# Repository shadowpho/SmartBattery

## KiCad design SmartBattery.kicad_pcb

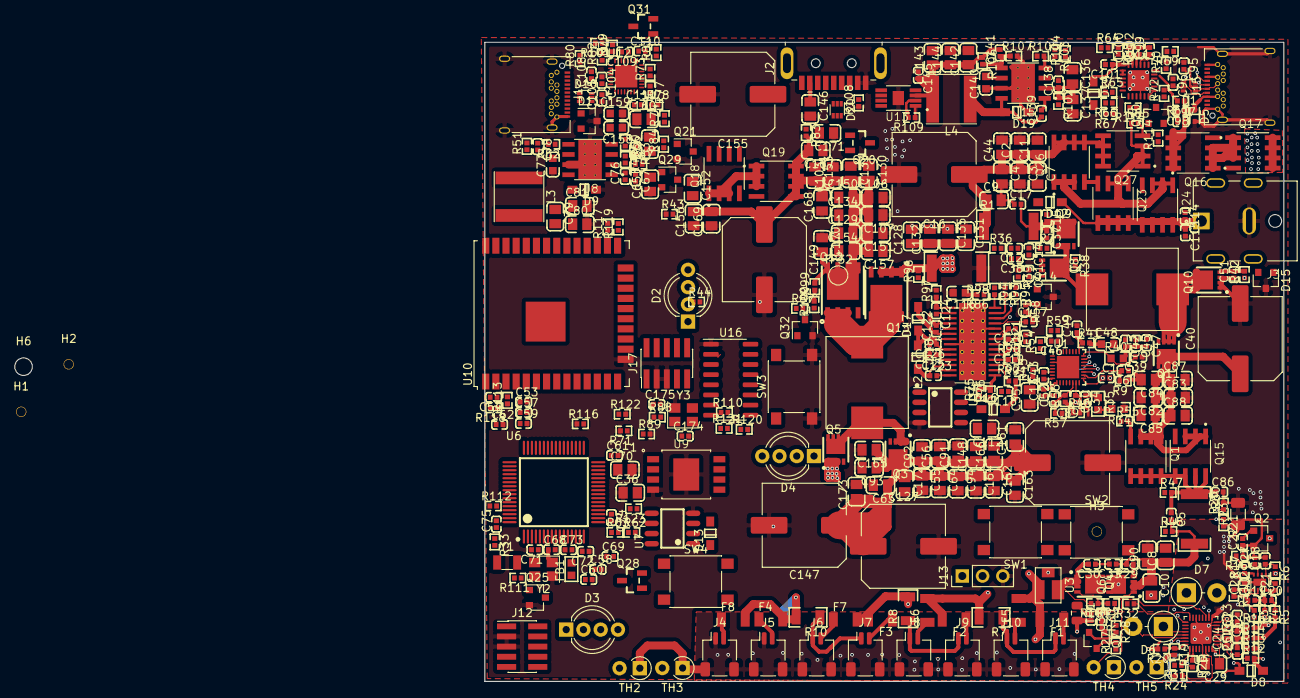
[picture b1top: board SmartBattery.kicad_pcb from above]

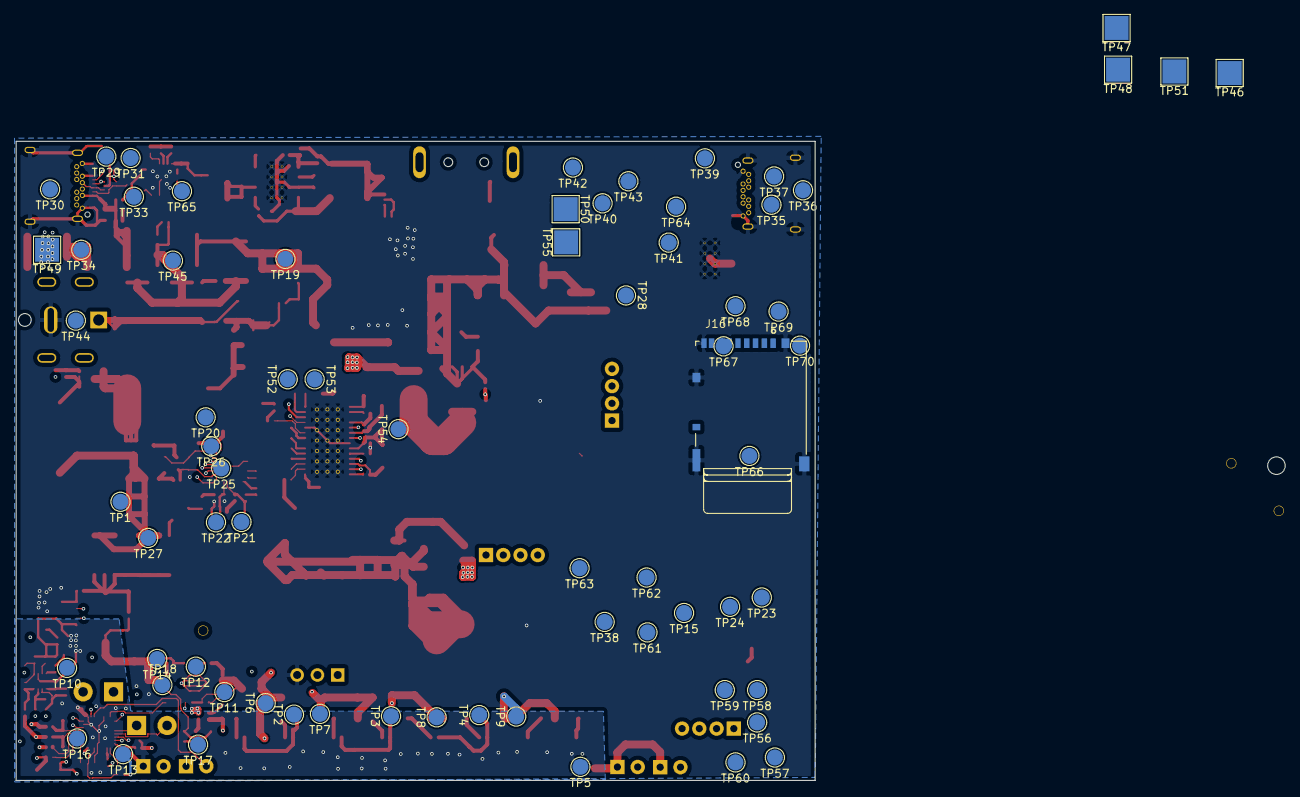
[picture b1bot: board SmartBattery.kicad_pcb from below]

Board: 4 copper layers, 100.0 x 80.0 mm, 481 parts (70 on the bottom side), 267 nets.

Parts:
C1, C6, C34: 0.1uF 6.3v; 0402_C
C2, C3, C4, C7, C8, C9, C10, C11, C65, C66, C82, C83, C84, C85, C136, C137: 10u; 0805_C
C5: 0.1u; 0402_C
C12: DNP; 0402_C
C13, C86, C97, C98, C99, C100, C101, C102, C108, C109, C110, C111: 1uF 25v; 0402_C
C14, C15, C17, C38, C124: 33nF; 0402_C
C16, C40, C89, C127, C147, C149, C155: 470u; C_Elec_10x10.2
C18, C19, C20, C21, C23, C24, C25, C26, C32, C53, C54, C57, C59, C61, C62, C69, C72, C73, C74, C75: 0.1u 6.3v; 0402_C
C22, C43, C46, C145: 0.1uF 25v; 0402_C
C27, C28: 0.1u 20v; 0402_C
C29, C35: 2.2u 50v; 0805_C
C30, C33: 0.1u 50v; 0402_C
C31, C122, C123: 0.1uF; 0402_C
C36, C70, C112: 2.2u 6.3v; 0805_C
C37, C41, C42, C45, C51, C95, C96, C104, C105, C117: 150pF; 0402_C
C39: 33pF; 0402_C
C44, C55, C56, C63, C64, C79, C80, C81, C87, C88, C90, C91, C92, C93, C94, C142, C143, C144, C146, C148, C161, C162, C163, C164, C165, C166, C172, C173: 22u; 0805_C
C47: 1.5nF; 0402_C
C48: 680pF; 0603_C
C49: 15pF; 0402_C
C50, C52: 1uF 16v; 0402_C
C58, C60: 15 pF 0402; 0402_C
C67, C76, C138, C139: 0.1u 25v; 0402_C
C68, C71, C174, C175: 12pF 0402; 0402_C
C77, C140: 8.2nF; 0603_C
C78, C141: 220pF; 0402_C
C103, C106, C107, C128, C129, C130, C131, C132, C133, C134, C135, C150, C151, C152, C153, C154, C156, C157, C160, C167, C168, C169, C170, C171: 10u 50v; 0805_C
C114, C115, C118, C125, C126: 1uF 50v; 0402_C
C116: 4.7n; 0603_C
C119: 47n; 0402_C
C120: 33n; 0402_C
C121: 68p; 0402_C
C158, C159: 1uF 50v; 0603_C
D1, D10, D20: ESDA6V8AV6; SOT-563
D2, D3, D4: LED_BARG; LED_D5.0mm-4_RGB_Wide_Pins
D5: PESD24VS1UB-N; SOD-523
D6, D7: LED; D_DO-15_P3.81mm_Vertical_AnodeUp
D8, D9, D12, D13, D14, D16, D17, D18, D19: B5817W-5819W; SOD-123
D11, D15: NUP3105LT1G; SOT-23
F1, F2, F3, F4, F5, F6, F7, F8: Fuse_Small; 1206
FB1: Ferrite_Bead_Small; 0603_L
H1, H2, H3: MountingHole; MountingHole_1.152mm_JLPCB
H4, H5, H6: MountingHole; MountingHole_2.2mm_M2
J1, J15: USB_C_Receptacle_USB2.0; USB_C_Receptacle_Amphenol_12401548E4-2A
J2: ST-USB-003A; USB3_A_Plug_Wuerth_692112030100_Horizontal
J3: JACK-C-PC-10A-RA(R); GLOBTECK_JACK-C-PC-10A-RA(R)
J4, J5, J6, J7, J8, J9, J10, J11: JST 2P-1.0; JST_SH_SM02B-SRSS-TB_1x02-1MP_P1.00mm_Horizontal
J12, J17: Conn_02x05_Odd_Even; PinHeader_2x05_P1.27mm_Vertical_SMD
J13: Conn_01x03_Male; PinHeader_1x03_P2.54mm_Vertical
J16: DM3AT-SF-PEJM5; HRS_DM3AT-SF-PEJM5
L1, L2: MWSA1004-2R2MT; L_10.3x11.5_H4
L3, L4: 6.8uH 47mO SWPA6028S6R8MT; L_Taiyo-Yuden_NR-60xx
Q1, Q15, Q16, Q17, Q18, Q19, Q23, Q24, Q26, Q27: VBA2625; SOIC127P600X175-8N
Q2, Q7, Q14, Q25: 2n7002K; SOT-23
Q3, Q4, Q5, Q6, Q8, Q9, Q10, Q11: AON7400A; SON-8_3.3X3.3MM
Q12, Q13: BSC067N06LS3; DFN-8_5X6MM
Q20, Q28: LBSS84LT1G; SOT-23(SOT-23-3)
Q21, Q29, Q30, Q32: 2N7002; SOT-23
Q31: AO3401A; SOT-23(SOT-23-3)
R1, R60, R98: 0.01; 2512_R
R2, R36: 4.7; 0402_R
R3, R4, R5, R6, R12, R43, R114: 1k; 0402_R
R7, R8, R10: 1 mOhm; 1206_R
R9: 33k; 0402_R
R11, R13, R14, R15, R21, R25, R26, R117, R118, R119: 100; 0402_R
R16, R51: 51k; 0402_R
R17, R22, R24, R27, R31, R32, R66, R67, R68, R70, R71, R78, R79, R80, R82: 5.1k; 0402_R
R18: 10Meg; 0402_R
R19, R53, R57, R58: DNP; 0402_R
R20, R33, R37, R38, R39, R42, R49, R54, R55, R64, R77, R93, R94, R95, R102, R103: 0; 0402_R
R23: 0.001; R_1206_3216Metric
R28, R30, R41, R86, R101, R115: 10k; 0402_R
R29: 10M; 0402_R
R34: 27k; 0603_R
R35: 110k; 0603_R
R40: 40.2k; 0603_R
R44, R62, R63, R65, R69, R72, R73, R75, R76, R81, R83, R84, R85, R88, R89, R108, R110, R111, R112, R113, R116, R120, R121, R122: 100k; 0402_R
R45, R96, R97: 1; 0402_R
R46, R47, R48: 10; 0402_R
R50, R100, R105: 20k; 0402_R
R52, R107: 15k; 0402_R
R56, R59: 110k; 0402_R
R61, R74, R87, R91, R104: ??; 0402_R
R90: 68.1k; 0402_R
R92: 93.1k; 0402_R
R99: 280k; 0402_R
R106: ???; 0402_R
R109: 22.1k; 0402_R
R123: 50k; 0402_R
SW1, SW2, SW3, SW4: SW_Push; SW_Push_1P1T_NO_6x6mm_H9.5mm
TH1: NCP18WF104F03; R_0805_2012Metric
TH2, TH3, TH4, TH5: NXRT15WB473FA1B030; D_A-405_P2.54mm_Vertical_AnodeUp
TP1, TP2, TP3, TP4, TP5, TP6, TP7, TP8, TP9, TP10, TP11, TP12, TP13, TP14, TP15, TP16, TP17, TP18, TP19, TP20, TP21, TP22, TP23, TP24, TP25, TP26, TP27, TP28, TP29, TP30, TP31, TP32, TP33, TP34, TP35, TP36, TP37, TP38, TP39, TP40, TP41, TP42, TP43, TP44, TP45, TP52, TP53, TP54, TP56, TP57, TP58, TP59, TP60, TP61, TP62, TP63, TP64, TP65, TP66, TP67, TP68, TP69, TP70: TestPoint; TestPoint_Pad_D2.0mm
TP46, TP47, TP48, TP49, TP50, TP51, TP55: TestPoint_Flag; TestPoint_Pad_3.0x3.0mm
U1: BQ25703ARSNR; VQFN-32_4X4X04P
U2: BQ294706DSGR; WSON-8-1EP_2x2mm_P0.5mm_EP0.9x1.6mm
U3: ITV4030
U4: BQ40Z50; QFN-32-1EP_4x4mm_P0.4mm_EP2.65x2.65mm
U5: LM5175PWPR; IC_TPS61196PWPRQ1
U6: STM32F730R8T6; TQFP-64_10X10X05P
U7: LY68L6400SLIT; SOP-8_150MIL
U8, U15: LMR14030SDDAR; NOPB
U9: FS35ND01G-S1Y2QWFI000; WSON8_8x6mm
U10: ESP32-WROOM-32U
U11: STUSB4500; QFN-24-1EP_4x4mm_P0.5mm_EP2.7x2.6mm
U12: STUSB4700; VQFN-32_4X4X04P
U13: TPS2511DGNR; SOP65P490X110-9N
U14: MCP6002-xMC; SOIC-8_150MIL
U16: CH340G; SOIC-16_3.9x9.9mm_P1.27mm
Y1: Q13FC1350000400; Crystal_SMD_3215-2Pin_3.2x1.5mm
Y2: 24MHz; Crystal_SMD_3225-4Pin_3.2x2.5mm
Y3: 12MHz; Crystal_SMD_3225-4Pin_3.2x2.5mm

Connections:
+3.3VP: C36.2, C53.1, C54.1, C57.1, C59.1, C61.1, C62.1, C74.1, C75.1, C78.2, C79.1, C80.1, C81.1, C112.2, D3.2, D4.2, FB1.1, J12.1, J16.4, J17.1, L3.2, R33.1, R51.1, R111.2, SW4.2, U6.19, U6.32, U6.48, U6.64, U7.8, U9.8, U10.2, U14.8
/5V_ENABLE: R108.2, U13.5
/ADAPTER_IN: C2.1, C3.1, C4.1, C7.1, C9.1, C11.1, C16.1, C44.1, Q17.5, Q17.6, Q17.7, Q17.8, Q26.5, Q26.6, Q26.7, Q26.8, Q27.5, Q27.6, Q27.7, Q27.8, R1.1, R36.1, TP19.1, TP49.1
/BARREL_RAW: C114.2, C115.1, D12.2, D15.1, D15.2, J3.1, Q23.5, Q23.6, Q23.7, Q23.8, Q24.5, Q24.6, Q24.7, Q24.8, R110.1, TP44.1
/BATT_INT_N: TP15.1, U4.15, U6.57
/BATT_PACK_P: C5.2, C8.1, C10.1, C33.1, C90.1, Q6.1, Q6.2, Q6.3, Q7.2, R28.2, R29.2, R48.2, R60.2, TP18.1
/BATT_SHUTDOWN_N: R32.2, U6.62
/BATT_SMB_C: J13.2, TP16.1, U4.19, U6.61
/BATT_SMB_D: J13.1, TP17.1, U4.18, U6.59
/BYPASS_VSYS: D12.1, D13.1, D14.1, R37.2, R102.2
/Barrel_Jack_Input/BARREL_ENABLE: Q25.1, R116.2
/CURRENT_TRIP: U14.1, U14.6
/Charger/REGN: C35.2, R46.1, R56.1, R59.1, U1.28
/Charger/VSYS: C40.1, C55.1, C56.1, C63.1, C64.1, C82.1, C83.1, C84.1, C85.1, C87.1, C88.1, C89.1, C91.1, C92.1, C93.1, C94.1, C127.1, C147.1, C148.1, C161.1, C162.1, C163.1, C164.1, C165.1, C166.1, C172.1, C173.1, D13.2, D16.2, Q1.1, Q1.2, Q1.3, Q3.5, Q3.6, Q3.7, Q3.8, Q11.5, Q11.6, Q11.7, Q11.8, Q15.1, Q15.2, Q15.3, TP1.1, TP28.1, TP51.1, U1.22, U5.3
/DAC1: U6.20, U14.3
/DAC2: R123.2, U6.21
/IADP: C34.1, R35.1, U1.8, U6.11
/IBAT: C1.1, U1.9, U6.24
/INPUT_TYPEC_RAW: C97.2, C98.1, C101.1, D5.2, D14.2, J15.A4, J15.A9, J15.B4, J15.B9, Q16.5, Q16.6, Q16.7, Q16.8, Q30.3, R61.1, R88.1, R115.2, TP31.1, U11.24
/INPUT_USB_DM: D1.1, D1.3, J15.A6, J15.A7, J15.B6, J15.B7
/MCU/ADC1_IN10: R88.2, R89.1, U6.8
/MCU/ADC1_IN11: R110.2, R120.1, U6.9
/MCU/ADC1_IN12: R121.2, R122.1, U6.10
/MCU/BOOT: R112.2, SW4.1, U6.60
/MCU/DET: J16.SWA, TP66.1, U10.8
/MCU/ESP32_SERIAL_BL: R119.1, U10.25
/MCU/ESP32_UART_RX: U6.42, U10.34
/MCU/ESP32_UART_TX: U6.43, U10.35
/MCU/ESP32_WAKE: R117.1, U10.26
/MCU/GPIO_ENABLE_ESP32: J17.10, R113.2, R118.1, U10.3
/MCU/NRST: J12.10, R111.1, SW3.1, TP56.1, TP60.1, U6.7
/MCU/QUADSPI_BK1_IO0: U6.40, U7.5
/MCU/QUADSPI_BK1_IO1: U6.51, U7.2
/MCU/QUADSPI_CLK: U6.27, U7.6
/MCU/QUASPI_BK1_NCS: U6.58, U7.1
/MCU/SPI2_MISO: U6.35, U9.5
/MCU/SPI2_MOSI: U6.36, U9.2
/MCU/SPI2_NSS: U6.33, U9.1
/MCU/SPI2_SCK: U6.34, U9.6
/MCU/SWDCLK: J12.4, TP58.1, U6.49
/MCU/SWDIO: J12.2, TP57.1, U6.46
/MCU/SWO: J12.6, TP59.1, U6.55
/MCU/TCK: J17.4, U10.16
/MCU/TDI: J17.8, U10.14
/MCU/TDO: J17.6, U10.23
/MCU/TMS: J17.2, U10.13
/MCU/UART5_RX: U6.54, U10.28
/MCU/UART5_TX: U6.53, U10.27
/OUTPUT_ALERT_N: R80.1, U12.9
/OUTPUT_ENABLE: R76.1, U5.1, U14.7
/OUTPUT_TYPEC_MCUPWR: Q21.1, Q31.1, R44.2, R77.1, R84.2
/OUTPUT_TYPEC_SCL: R78.1, U12.7
/OUTPUT_TYPEC_SDA: R79.1, U12.8
/OUTPUT_USB_DM: D10.1, D10.3, J1.A6, J1.A7, J1.B6, J1.B7
/OUTPUT_VOLTAGE: C103.1, C106.1, C107.2, C128.1, C129.2, C130.2, C131.2, C132.1, C133.2, C134.2, C135.2, C149.1, C150.2, C151.2, C152.2, C153.2, C154.2, C155.1, C156.2, C157.2, C167.2, C168.2, C169.2, C170.2, C171.2, Q12.0, Q12.5, Q12.6, Q12.7, Q12.8, Q19.5, Q19.6, Q19.7, Q19.8, Q20.2, R83.2, R87.2, R95.1, R99.2, R121.1, TP50.1, TP55.1, U5.12
/OutputStage/HDRV_1: Q3.4, U5.27
/OutputStage/HDRV_2: Q12.4, U5.19
/OutputStage/LDRV_1: Q5.4, U5.25
/OutputStage/LDRV_2: Q13.4, U5.21
/OutputStage/SW1: C123.2, L2.2, Q3.1, Q3.2, Q3.3, Q5.5, Q5.6, Q5.7, Q5.8, U5.28
/OutputStage/SW2: C122.2, L2.1, Q12.1, Q12.2, Q12.3, Q13.0, Q13.5, Q13.6, Q13.7, Q13.8, U5.18
/Output_TYPEA/OUTPUT_CS_N: TP32.1, U13.4
/PSYS: C6.2, R9.2, U1.10, U6.26, U14.2
/Peripheral_3p3v/3p3_SWITCHED_NODE: C76.1, D9.1, L3.1, U8.8
/Peripheral_3p3v/5v0: C141.2, C142.1, C143.1, C144.1, C145.2, L4.2, R106.1, U13.3
/Peripheral_3p3v/5v0_SWITCHED_NODE: C139.1, D19.1, L4.1, U15.8
/Peripheral_3p3v/VSYS_IN_3p3: C65.2, C66.1, C67.1, R37.1, R49.2, U8.2
/Peripheral_3p3v/VSYS_IN_5p0: C136.2, C137.1, C138.1, R102.1, U15.2
/RESET_OVERCURRENT: R75.2, R76.2, U14.5
/Type_C_Output/2v7_local: C109.1, U12.23
/Type_C_Output/LOCAL_PWR: C110.1, R77.2, R78.2, R79.2, R80.2, U12.22
/Type_C_Output/VCONN: C111.1, Q31.3, U12.3
/Type_C_Output/VCONN_VOLTAGE: Q31.2, R44.1
/type_c_input/2v7_local: C100.1, U11.23
/type_c_input/INPUT_TYPEC_ALERT_N: R68.1, U11.19
/type_c_input/INPUT_TYPEC_SCL: R66.1, U11.7
/type_c_input/INPUT_TYPEC_SDA: R67.1, U11.8
/type_c_input/LOCAL_PWR: C102.1, R64.2, R66.2, R67.2, R68.2, U11.22
BAT_VN_0: C18.2, C22.1, C23.2, C27.2, C28.2, C29.2, J4.1, J4.MP, J5.1, J5.MP, J6.MP, J7.MP, J8.MP, J9.MP, J10.MP, J11.MP, Q2.2, R16.1, R19.2, R21.2, R23.1, SW1.2, SW2.2, TH2.1, TH3.1, TH4.1, TH5.1, TP5.1, U2.6, U2.9, U4.7, U4.9, U4.14, U4.29, U4.33
BAT_VN_1: J6.1, J7.1, R10.1, TP4.1
BAT_VN_2: J8.1, J9.1, R8.1, TP3.1
BAT_VN_3: J10.1, J11.1, R7.1, TP2.1
BAT_VP_0: F4.2, F8.2, R6.2, R10.2, R15.2, TP9.1
BAT_VP_1: F3.2, F7.2, R5.2, R8.2, R14.2, TP8.1
BAT_VP_2: F2.2, F6.2, R4.2, R7.2, R13.2, TP7.1
BAT_VP_3: D8.2, F1.2, F5.2, R3.2, R12.2, TP6.1, U3.1
FUSE_HEATER: C22.2, Q2.1, R16.2, R17.2, R31.2, TP10.1
GND: C1.2, C2.2, C3.2, C4.2, C6.1, C7.2, C8.2, C9.2, C10.2, C11.2, C13.1, C14.2, C15.1, C16.2, C17.1, C34.2, C35.1, C36.1, C37.2, C38.1, C39.1, C40.2, C41.1, C42.1, C44.2, C45.1, C47.1, C48.2, C49.2, C50.2, C51.1, C52.2, C53.2, C54.2, C55.2, C56.2, C57.2, C58.2, C59.2, C60.2, C61.2, C62.2, C63.2, C64.2, C65.1, C66.2, C67.2, C68.2, C69.1, C70.2, C71.2, C72.1, C73.1, C74.2, C75.2, C77.1, C79.2, C80.2, C81.2, C82.2, C83.2, C84.2, C85.2, C86.2, C87.2, C88.2, C89.2, C90.2, C91.2, C92.2, C93.2, C94.2, C95.1, C96.1, C97.1, C98.2, C99.2, C100.2, C101.2, C102.2, C103.2, C104.1, C105.1, C106.2, C107.1, C108.2, C109.2, C110.2, C111.2, C112.1, C114.1, C115.2, C116.2, C117.2, C118.1, C119.1, C120.1, C121.2, C125.2, C126.2, C127.2, C128.2, C129.1, C130.1, C131.1, C132.2, C133.1, C134.1, C135.1, C136.1, C137.2, C138.2, C140.1, C142.2, C143.2, C144.2, C145.1, C146.2, C147.2, C148.2, C149.2, C150.1, C151.1, C152.1, C153.1, C154.1, C155.2, C156.1, C157.1, C158.1, C159.2, C160.1, C161.2, C162.2, C163.2, C164.2, C165.2, C166.2, C167.1, C168.1, C169.1, C170.1, C171.1, C172.2, C173.2, C174.2, C175.2, D1.2, D5.1, D9.2, D10.2, D11.3, D15.3, D19.2, D20.2, J1.A1, J1.A12, J1.B1, J1.B12, J1.S1, J2.4, J2.5, J3.2, J12.3, J12.5, J13.3, J15.A1, J15.A12, J15.B1, J15.B12, J15.S1, J16.6, J16.P1, J16.P2, J16.P3, J16.P4, J16.SWB, J17.3, J17.5, Q8.1, Q8.2, Q8.3, Q10.1, Q10.2, Q10.3, Q14.3, Q21.2, Q25.2, Q32.2, R9.1, R23.2, R25.2, R30.1, R34.1, R43.1, R50.1, R52.2, R53.1, R57.1, R58.2, R62.2, R65.1, R71.2, R72.1, R73.1, R75.1, R84.1, R89.2, R90.1, R92.1, R93.1, R94.1, R97.2, R98.1, R100.1, R104.1, R105.1, R107.2, R108.1, R109.1, R112.1, R113.1, R114.1, R116.1, R120.2, R122.2, SW3.2, TP46.1, TP47.1, TP48.1, U1.0, U1.27, U5.10, U5.22, U5.29, U5.30, U5.31, U5.32, U5.33, U5.34, U5.35, U5.36, U5.37, U5.38, U5.39, U5.40, U5.41, U5.42, U5.43, U5.44, U5.45, U5.46, U5.47, U5.48, U5.49, U5.50, U6.12, U6.18, U6.31, U6.47, U6.63, U7.4, U8.7, U8.9, U8.10, U8.11, U8.12, U8.13, U8.14, U8.15, U8.16, U8.17, U9.4, U9.9, U10.1, U10.15, U10.38, U11.10, U11.25, U12.1, U12.5, U12.10, U12.24, U13.1, U13.9, U14.4, U15.7, U15.9, U15.10, U15.11, U15.12, U15.13, U15.14, U15.15, U15.16, U15.17, U16.1, Y2.2, Y2.4, Y3.2, Y3.4
unnamed: C5.1, C86.1, Q1.5, Q1.6, Q1.7, Q1.8, Q15.5, Q15.6, Q15.7, Q15.8, R47.2, R60.1
unnamed: C12.1, C14.1, R2.2, TP21.1, U1.2
unnamed: C12.2, C38.2, R36.2, TP22.1, U1.3
unnamed: C13.2, R45.1, U1.1
unnamed: C15.2, C17.2, C37.1, Q9.5, Q9.6, Q9.7, Q9.8, R1.2, R2.1, R45.2
unnamed: C18.1, C21.2, R6.1, U2.5
unnamed: C19.1, R3.1, R11.2, U2.2
unnamed: C19.2, C20.1, R4.1, U2.3
unnamed: C20.2, C21.1, R5.1, U2.4
unnamed: C23.1, C26.2, R15.1, U4.5
unnamed: C24.1, R12.1, U4.2
unnamed: C24.2, C25.1, R13.1, U4.3
unnamed: C25.2, C26.1, R14.1, U4.4
unnamed: C27.1, U2.7
unnamed: C28.1, R11.1, U2.1
unnamed: C29.1, U4.1
unnamed: C30.1, C33.2
unnamed: C30.2, Q4.1, Q4.2, Q4.3, R18.2, U3.3
unnamed: C31.1, TH1.1, U4.23
unnamed: C31.2, D8.1, R20.2, TH1.2, U4.32
unnamed: C32.1, R25.1, U4.8
unnamed: C32.2, R21.1, U4.6
unnamed: C39.2, R40.1, U1.16
unnamed: C41.2, Q8.4, R39.2
unnamed: C42.2, C45.2, C47.2, R40.2
unnamed: C43.1, L1.2, Q8.5, Q8.6, Q8.7, Q8.8, Q9.1, Q9.2, Q9.3, TP20.1, U1.32
unnamed: C43.2, U1.30
unnamed: C46.1, L1.1, Q10.5, Q10.6, Q10.7, Q10.8, Q11.1, Q11.2, Q11.3, U1.23
unnamed: C46.2, U1.25
unnamed: C48.1, R41.2
unnamed: C49.1, R41.1, U1.17
unnamed: C50.1, R46.2, U1.7
unnamed: C51.2, Q10.4, R42.2
unnamed: C52.1, R56.2, R57.2, U1.6
unnamed: C58.1, U6.3, Y1.2
unnamed: C60.1, U6.4, Y1.1
unnamed: C68.1, U6.6, Y2.1
unnamed: C69.2, C70.1, U6.30
unnamed: C71.1, U6.5, Y2.3
unnamed: C72.2, C73.2, FB1.2, TP24.1, U6.13
unnamed: C76.2, U8.1
unnamed: C77.2, U8.6
unnamed: C78.1, R51.2, R52.1, U8.5
unnamed: C95.2, D1.4, J15.B5, U11.4, U11.5
unnamed: C96.2, D1.5, J15.A5, U11.1, U11.2
unnamed: C99.1, U11.21
unnamed: C104.2, D10.4, J1.B5, U12.4
unnamed: C105.2, D10.5, J1.A5, U12.2
unnamed: C108.1, U12.21
unnamed: C116.1, R86.2
unnamed: C117.1, R86.1, U5.9
unnamed: C118.2, R91.1, U5.2
unnamed: C119.2, U5.5
unnamed: C120.2, U5.8
unnamed: C121.1, U5.7
unnamed: C122.1, D17.1, U5.20
unnamed: C123.1, D18.1, U5.26
unnamed: C124.1, R97.1, U5.15
unnamed: C124.2, R96.1, U5.16
unnamed: C125.1, R95.2, U5.24
unnamed: C126.1, D17.2, D18.2, TP54.1, U5.23
unnamed: C139.2, U15.1
unnamed: C140.2, U15.6
unnamed: C141.1, R106.2, R107.1, U15.5
unnamed: C146.1, D20.1, J2.1, U13.8
unnamed: C158.2, C159.1, C160.2, D11.1, D11.2, J1.A4, J1.A9, J1.B4, J1.B9, Q18.5, Q18.6, Q18.7, Q18.8, Q29.3, R74.1, R101.2, TP37.1
unnamed: C174.1, U16.7, Y3.1
unnamed: C175.1, U16.8, Y3.3
unnamed: D3.1, U10.12
unnamed: D3.3, U10.10
unnamed: D3.4, U10.11
unnamed: D4.1, U10.7
unnamed: D4.3, U10.9
unnamed: D4.4, U10.6
unnamed: D6.1, U4.20
unnamed: D6.2, D7.1, U4.21
unnamed: D7.2, U4.22
unnamed: D16.1, R91.2
unnamed: D20.3, J2.3, U13.6
unnamed: D20.6, J2.2, U13.7
unnamed: F1.1, J11.2
unnamed: F2.1, J9.2
unnamed: F3.1, J7.2
unnamed: F4.1, J5.2
unnamed: F5.1, J10.2
unnamed: F6.1, J8.2
unnamed: F7.1, J6.2
unnamed: F8.1, J4.2
unnamed: J1.A8, TP35.1
unnamed: J1.B8, TP36.1
unnamed: J15.A8, TP29.1
unnamed: J15.B8, TP30.1
unnamed: J16.1, U10.17
unnamed: J16.2, U10.18
unnamed: J16.3, U10.19
unnamed: J16.5, U10.20
unnamed: J16.7, U10.21
unnamed: J16.8, U10.22
unnamed: Q1.4, Q15.4, R55.2, TP27.1
unnamed: Q2.3, U3.2
unnamed: Q4.4, R18.1, R22.2, TP11.1
unnamed: Q4.5, Q4.6, Q4.7, Q4.8, Q6.5, Q6.6, Q6.7, Q6.8, R26.2, TP12.1
unnamed: Q6.4, Q7.3, R27.2, R29.1, TP14.1
unnamed: Q7.1, R30.2
unnamed: Q9.4, R38.1
unnamed: Q11.4, R54.2
unnamed: Q5.1, Q5.2, Q5.3, Q13.1, Q13.2, Q13.3, R96.2, R98.2
unnamed: Q14.2, R58.1, R59.2, U1.18
unnamed: Q16.1, Q16.2, Q16.3, Q17.1, Q17.2, Q17.3, R69.1, TP34.1
unnamed: Q16.4, Q17.4, R69.2, R70.2
unnamed: Q18.1, Q18.2, Q18.3, Q19.1, Q19.2, Q19.3, R81.1, TP43.1
unnamed: Q18.4, Q19.4, R81.2, R82.2
unnamed: Q20.1, Q21.3, R83.1
unnamed: Q23.1, Q23.2, Q23.3, Q24.1, Q24.2, Q24.3, Q26.1, Q26.2, Q26.3, Q27.1, Q27.2, Q27.3, R85.1, TP45.1
unnamed: Q23.4, Q24.4, Q25.3, Q26.4, Q27.4, R85.2
unnamed: Q28.3, U16.3
unnamed: Q29.1, R101.1, U12.19
unnamed: Q29.2, R43.2
unnamed: Q30.1, R115.1, U11.9
unnamed: Q30.2, R114.2
unnamed: Q32.3, R87.1
unnamed: R17.1, U2.8
unnamed: R19.1, R20.1, U4.24
unnamed: R22.1, U4.31
unnamed: R24.1, U4.30
unnamed: R24.2, TP13.1
unnamed: R26.1, U4.26
unnamed: R27.1, U4.28
unnamed: R28.1, U4.27
unnamed: R31.1, U4.25
unnamed: R32.1, SW1.1, U4.16
unnamed: R33.2, U6.1
unnamed: R34.2, R35.2
unnamed: R38.2, U1.31
unnamed: R39.1, U1.29
unnamed: R42.1, U1.26
unnamed: R47.1, U1.20
unnamed: R48.1, U1.19
unnamed: R49.1, R53.2, U8.3
unnamed: R50.2, U8.4
unnamed: R54.1, U1.24
unnamed: R55.1, U1.21
unnamed: R61.2, U11.18
unnamed: R62.1, R63.1
unnamed: R65.2, TP65.1, U11.6
unnamed: R70.1, U11.16
unnamed: R71.1, TP64.1, U12.6
unnamed: R72.2, U11.12, U11.13
unnamed: R73.2, U12.13
unnamed: R74.2, U12.18
unnamed: R82.1, U12.20
unnamed: R90.2, U5.6
unnamed: R92.2, U5.4
unnamed: R93.2, TP52.1, U5.13
unnamed: R94.2, TP53.1, U5.14
unnamed: R99.1, R100.2, R123.1, U5.11
unnamed: R103.1, R104.2, U15.3
unnamed: R105.2, U15.4
unnamed: R109.2, U13.2
unnamed: SW2.1, U4.17
unnamed: TH2.2, U4.13
unnamed: TH3.2, U4.12
unnamed: TH4.2, U4.11
unnamed: TH5.2, U4.10
unnamed: TP25.1, U1.14
unnamed: TP26.1, U1.15
unnamed: TP33.1, U11.15
unnamed: TP38.1, U7.3
unnamed: TP39.1, U12.17
unnamed: TP40.1, U12.11
unnamed: TP41.1, U12.12
unnamed: TP42.1, U12.14
unnamed: TP61.1, U7.7
unnamed: TP62.1, U9.3
unnamed: TP63.1, U9.7
unnamed: TP67.1, U10.29
unnamed: TP68.1, U10.30
unnamed: TP69.1, U10.31
unnamed: TP70.1, U10.37

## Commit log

2020-12-10 Initial CI
2020-12-12 added some more protection connection
2020-12-14 Almost done with battery protection.
2020-12-16 Battery protection sch done. Assigned 99% of footprints. Layout is gonna be rough.
2020-12-17 Finished battery protection, starting charger page
2020-12-18 Added capacitors, inductors to charger page. Fixed capacitor sizes.
2020-12-19 Added bunch of cap to charger, made footprint for diode + fuse
2020-12-20 Finished Charger section, assigned all footprints. Next is output and then peripherals.
2020-12-21 Adding lots of changes. Started output Stage
2020-12-25 Lots of changes for MFG: parts info
2020-12-30 Switching over to jlpcb
2020-12-31 Replaced old charger to support JLC assembly. Very close now!
2021-01-04 Both type-c ports are done! Only outputstage left.
2021-01-05 Added final touches to barrel jack and feedforward.
    Need to finish output stage, then add screw terminals.
2021-01-11 Type_A_implemented. Sch "locked". PCB Layout started.
    *Changelog:
    *Type-a switching regulator (TBD -- need to check inductor,caps, stability. Maybe check both peripherial inductors?)
    *Type-A load switch + connector + esd
    *started layout..
    *found out that my footprint for n fet is wrong. Fixing now, need to replace all of those.
2021-01-15 Much layout. Wow
2021-01-17 Layout placed type-c + barrel jack
2021-01-21 Much layout wow.
2021-01-26 Almost connected MCU + ESP32 added leds addedd uart usb cleaned up type-c I/O -- STILL NEED TO level shift I2C
2021-01-27 lots of GPIO connectivity changes. fixed no PD on input fixed CH340G leakage. can otherwise power from GPIO. added fet for powering VCONN from 3v/5v NEED TO ADD OVERCURRENT
2021-01-29 Modified connections, added current limit
